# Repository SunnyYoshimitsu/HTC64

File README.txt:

# Y!6502
Think Ben Eater's 6502 but modified....a modified BE6592...the Y!6502....

I modified this computer to have 2 VIA chips instead of just one since I think having more GPIO will allow it to be used as a more conventional microcontroller. Also I changed the memory layout and add a larger RAM. So the memory layout ended up being inverted to Ben's, 32k of RAM and 16k of ROM. There's an expansion slot in the middle designed to take a stock Ben Eater's GPU with its !DMA config or any other peripherals you want. The expansion slot is mapped to A000 - BFFF. 

Note there's a VGA output and associtated resistors, however there are no GPU to drive it. This is for the expansion slot. I am planning a "modified" BE6502 GPU that uses a dual port RAM so that the CPU can run at 100% capacity. Now this computer is basically everything that the BE6502 is except for the GPU but ofcourse you don't have to populate everything. 

I'm porting Wozmon to this modifed BE6502 since the UART is in a different place and it does support a keyboard. I will update this repo as soon as I'm done with it. 

If you have any question or ideas please don't hesitate to hit me up! I am an active user in the r/beneater subreddit. 
Profile: https://www.reddit.com/user/YoshimitsuSunny

Memory Layout: 
	Note: each section is 8k in size
0000 - 1FFF: RAM
2000 - 3FFF: RAM 
4000 - 5FFF: RAM 
6000 - 7FFF: RAM
8000 - 9FFF: DDRAM 
A000 - BFFF: Peripheral
A200 - UART
A400 - A40F: I/O Timer 1
  Reg A: GPIO
  Reg B: P/S 2
A800 - A80F: I/O Timer 2
  Reg A: GPIO
  Reg B: GPIO
C000 - DFFF: ROM (lower address) 
E000 - FFFF: ROM (higher address)

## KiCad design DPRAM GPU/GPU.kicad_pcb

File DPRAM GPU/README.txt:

The PCB version is incomplete!!!!!! Don't use it. I'll fix it at a later date. However, the schematic should be correct. Have fun!

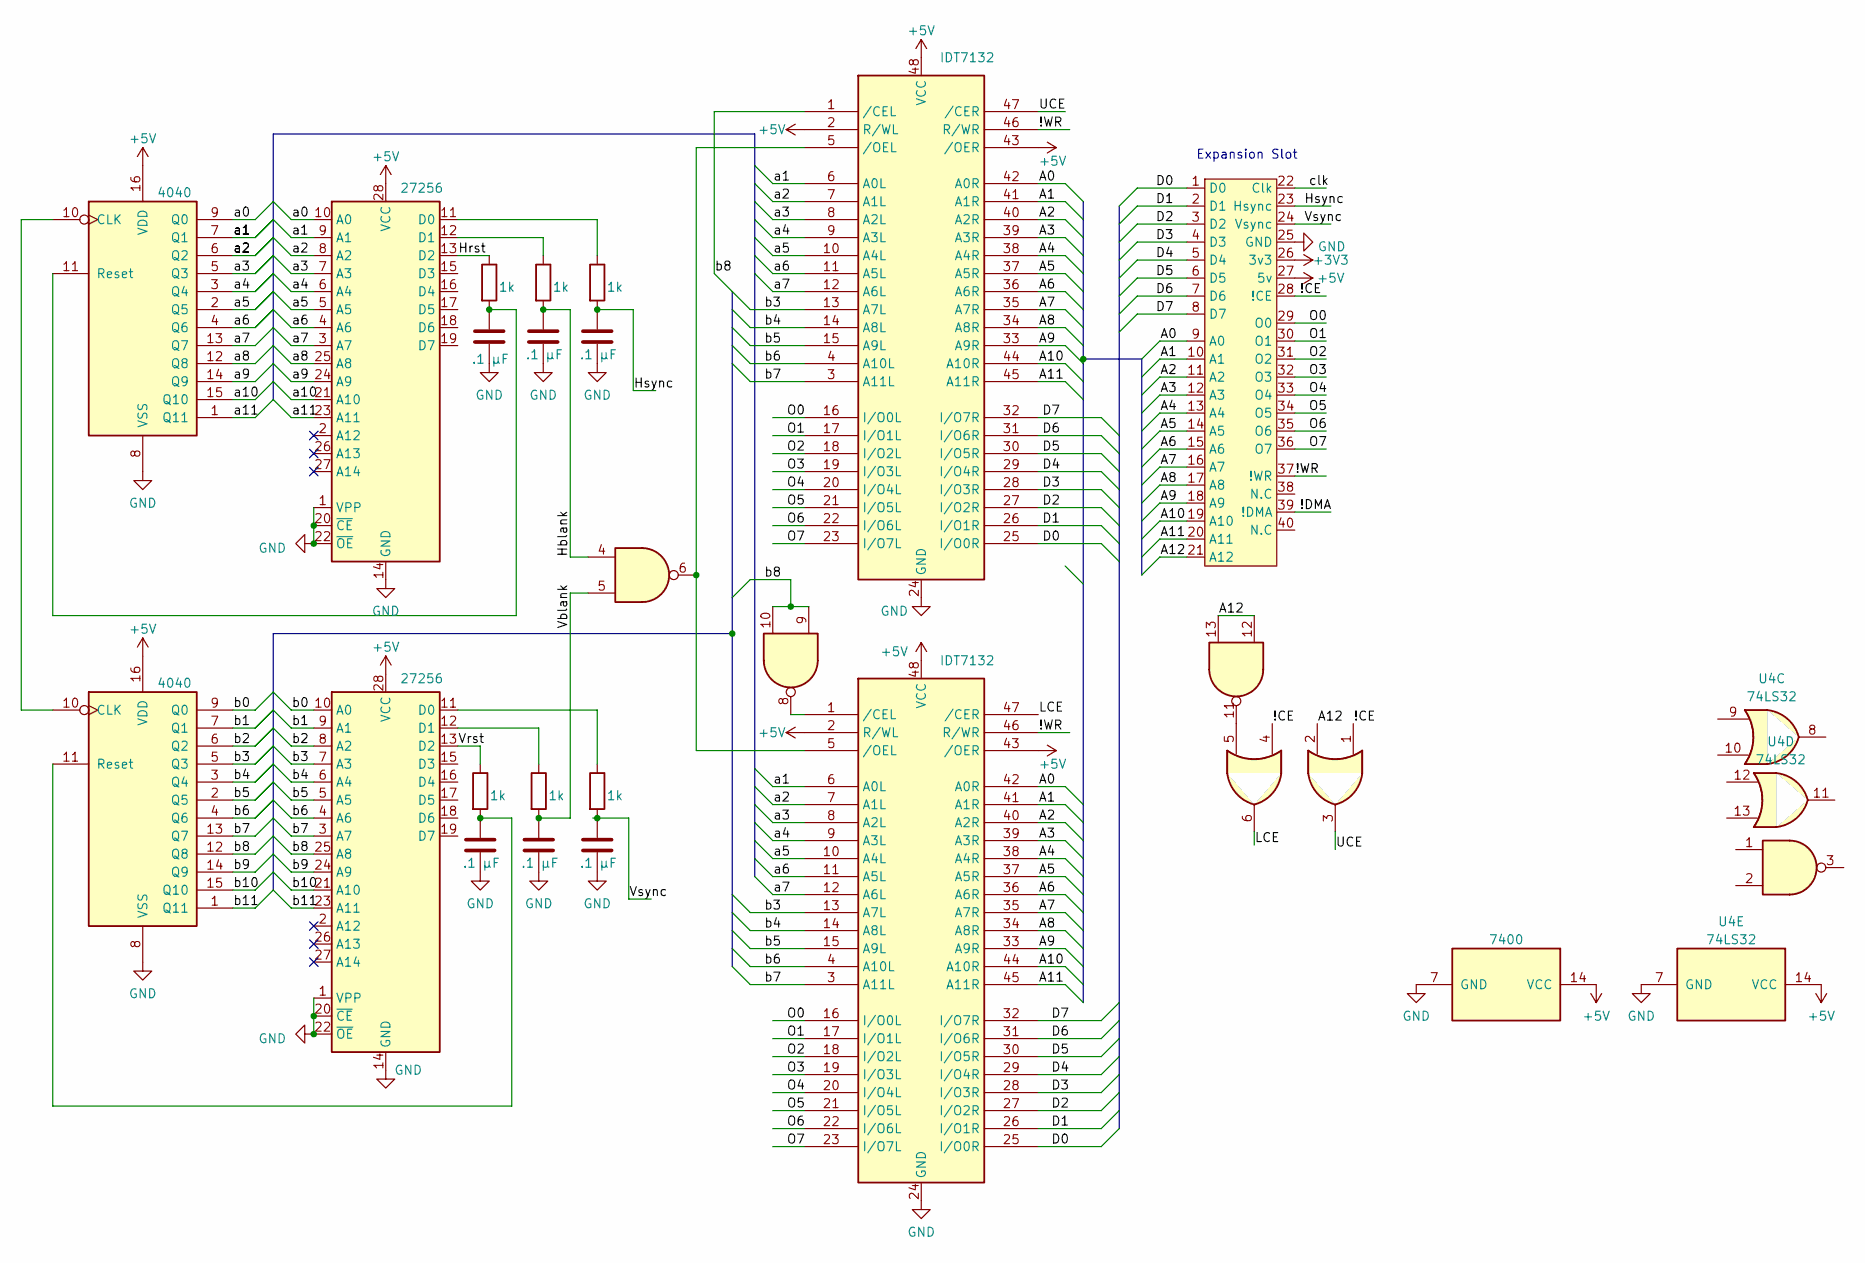
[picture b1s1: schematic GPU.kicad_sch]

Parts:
C1, C2, C3, C4, C5, C6: .1 μF; C_Disc_D3.4mm_W2.1mm_P2.50mm
R1, R2, R3, R4, R5, R6: 1k; R_Axial_DIN0207_L6.3mm_D2.5mm_P7.62mm_Horizontal
U1, U3: 4040; DIP-16_W7.62mm_Socket
U2, U8: 27256; DIP-28_W15.24mm_Socket
U4: 74LS32; DIP-14_W7.62mm
U5, U6: IDT7132; DIP-48_W15.24mm_Socket
U7: 7400; DIP-14_W7.62mm_Socket
~1: Y!6502 exp

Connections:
+5V: U1.16 (VDD), U2.28 (VCC), U3.16 (VDD), U4.14 (VCC), U5.2 (R/WL), U5.43 (/OER), U5.48 (VCC), U6.2 (R/WL), U6.43 (/OER), U6.48 (VCC), U7.14 (VCC), U8.28 (VCC), ~1.27 (5v)
/!CE: U4.1, U4.4, ~1.28 (!CE)
/!WR: U5.46 (R/WR), U6.46 (R/WR), ~1.37 (!WR)
/A0: U5.42 (A0R), U6.42 (A0R), ~1.9 (A0)
/A1: U5.41 (A1R), U6.41 (A1R), ~1.10 (A1)
/A2: U5.40 (A2R), U6.40 (A2R), ~1.11 (A2)
/A3: U5.39 (A3R), U6.39 (A3R), ~1.12 (A3)
/A4: U5.38 (A4R), U6.38 (A4R), ~1.13 (A4)
/A5: U5.37 (A5R), U6.37 (A5R), ~1.14 (A5)
/A6: U5.36 (A6R), U6.36 (A6R), ~1.15 (A6)
/A7: U5.35 (A7R), U6.35 (A7R), ~1.16 (A7)
/A8: U5.34 (A8R), U6.34 (A8R), ~1.17 (A8)
/A9: U5.33 (A9R), U6.33 (A9R), ~1.18 (A9)
/A10: U5.44 (A10R), U6.44 (A10R), ~1.19 (A10)
/A11: U5.45 (A11R), U6.45 (A11R), ~1.20 (A11)
/A12: U4.2, U7.12, U7.13, ~1.21 (A12)
/D0: U5.25 (I/O0R), U6.25 (I/O0R), ~1.1 (D0)
/D1: U5.26 (I/O1R), U6.26 (I/O1R), ~1.2 (D1)
/D2: U5.27 (I/O2R), U6.27 (I/O2R), ~1.3 (D2)
/D3: U5.28 (I/O3R), U6.28 (I/O3R), ~1.4 (D3)
/D4: U5.29 (I/O4R), U6.29 (I/O4R), ~1.5 (D4)
/D5: U5.30 (I/O5R), U6.30 (I/O5R), ~1.6 (D5)
/D6: U5.31 (I/O6R), U6.31 (I/O6R), ~1.7 (D6)
/D7: U5.32 (I/O7R), U6.32 (I/O7R), ~1.8 (D7)
/Hblank: C2.1, R2.2, U7.4
/Hrst: R1.1, U8.13 (D2)
/Hsync: C3.1, R3.2, ~1.23 (Hsync)
/LCE: U4.6, U6.47 (/CER)
/O0: U5.16 (I/O0L), U6.16 (I/O0L), ~1.29 (O0)
/O1: U5.17 (I/O1L), U6.17 (I/O1L), ~1.30 (O1)
/O2: U5.18 (I/O2L), U6.18 (I/O2L), ~1.31 (O2)
/O3: U5.19 (I/O3L), U6.19 (I/O3L), ~1.32 (O3)
/O4: U5.20 (I/O4L), U6.20 (I/O4L), ~1.33 (O4)
/O5: U5.21 (I/O5L), U6.21 (I/O5L), ~1.34 (O5)
/O6: U5.22 (I/O6L), U6.22 (I/O6L), ~1.35 (O6)
/O7: U5.23 (I/O7L), U6.23 (I/O7L), ~1.36 (O7)
/UCE: U4.3, U5.47 (/CER)
/Vblank: C5.1, R5.2, U7.5
/Vrst: R4.1, U2.13 (D2)
/Vsync: C6.1, R6.2, ~1.24 (Vsync)
/a0: U1.9 (Q0), U8.10 (A0)
/a1: U1.7 (Q1), U5.6 (A0L), U6.6 (A0L), U8.9 (A1)
/a2: U1.6 (Q2), U5.7 (A1L), U6.7 (A1L), U8.8 (A2)
/a3: U1.5 (Q3), U5.8 (A2L), U6.8 (A2L), U8.7 (A3)
/a4: U1.3 (Q4), U5.9 (A3L), U6.9 (A3L), U8.6 (A4)
/a5: U1.2 (Q5), U5.10 (A4L), U6.10 (A4L), U8.5 (A5)
/a6: U1.4 (Q6), U5.11 (A5L), U6.11 (A5L), U8.4 (A6)
/a7: U1.13 (Q7), U5.12 (A6L), U6.12 (A6L), U8.3 (A7)
/a8: U1.12 (Q8), U8.25 (A8)
/a9: U1.14 (Q9), U8.24 (A9)
/a10: U1.15 (Q10), U8.21 (A10)
/a11: U1.1 (Q11), U8.23 (A11)
/b0: U2.10 (A0), U3.9 (Q0)
/b1: U2.9 (A1), U3.7 (Q1)
/b2: U2.8 (A2), U3.6 (Q2)
/b3: U2.7 (A3), U3.5 (Q3), U5.13 (A7L), U6.13 (A7L)
/b4: U2.6 (A4), U3.3 (Q4), U5.14 (A8L), U6.14 (A8L)
/b5: U2.5 (A5), U3.2 (Q5), U5.15 (A9L), U6.15 (A9L)
/b6: U2.4 (A6), U3.4 (Q6), U5.4 (A10L), U6.4 (A10L)
/b7: U2.3 (A7), U3.13 (Q7), U5.3 (A11L), U6.3 (A11L)
/b8: U2.25 (A8), U3.12 (Q8), U5.1 (/CEL), U7.9, U7.10
/b9: U2.24 (A9), U3.14 (Q9)
/b10: U2.21 (A10), U3.15 (Q10)
/b11: U2.23 (A11), U3.1 (Q11)
GND: C1.2, C2.2, C3.2, C4.2, C5.2, C6.2, U1.8 (VSS), U2.1 (VPP), U2.14 (GND), U2.20 (~CE), U2.22 (~OE), U3.8 (VSS), U4.7 (GND), U5.24 (GND), U6.24 (GND), U7.7 (GND), U8.1 (VPP), U8.14 (GND), U8.20 (~CE), U8.22 (~OE), ~1.25 (GND)
unnamed: U1.10 (CLK), U3.10 (CLK)
unnamed: C1.1, R1.2, U1.11 (Reset)
unnamed: R6.1, U2.11 (D0)
unnamed: R5.1, U2.12 (D1)
unnamed: C4.1, R4.2, U3.11 (Reset)
unnamed: U4.5, U7.11
unnamed: U5.5 (/OEL), U6.5 (/OEL), U7.6
unnamed: U6.1 (/CEL), U7.8
unnamed: R3.1, U8.11 (D0)
unnamed: R2.1, U8.12 (D1)

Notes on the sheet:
Expansion Slot

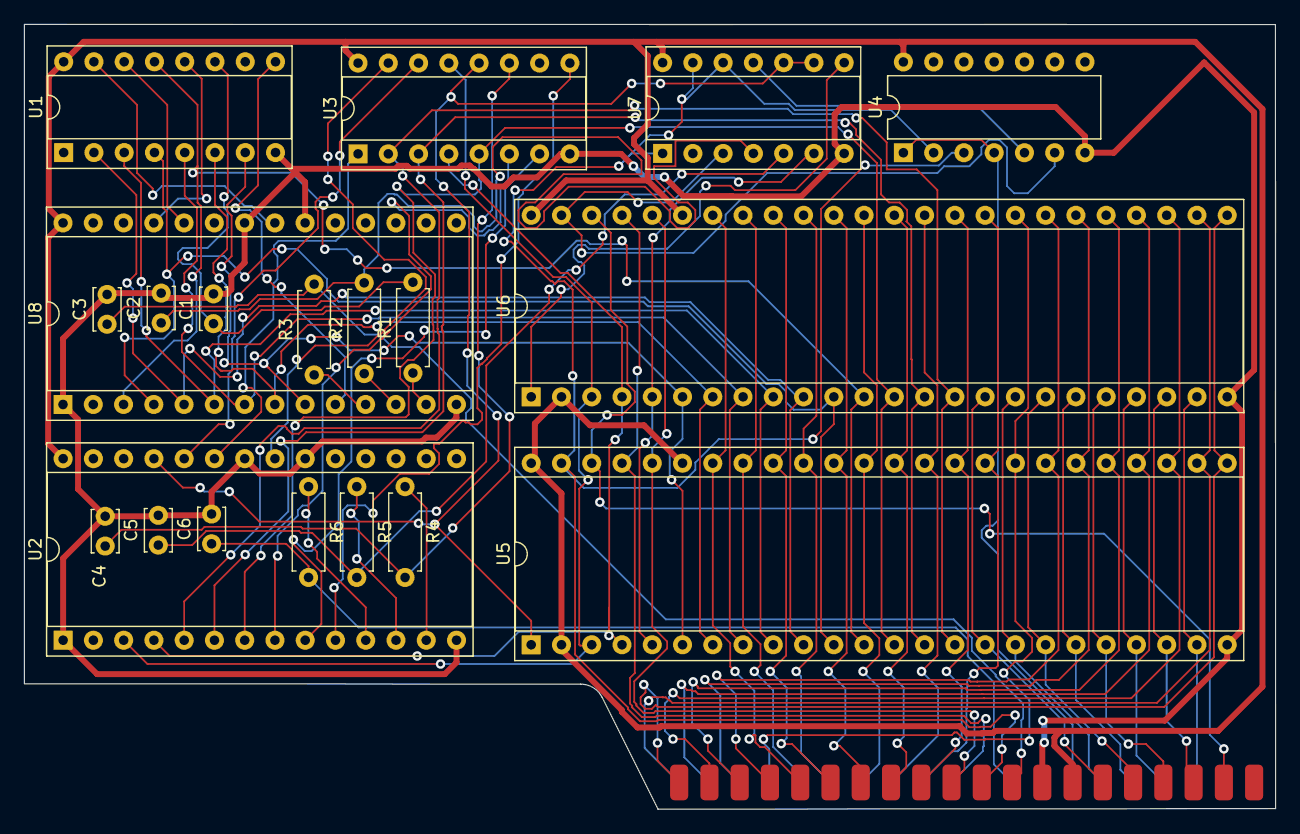
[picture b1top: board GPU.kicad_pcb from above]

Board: 2 copper layers, 105.0 x 65.9 mm, 20 parts (0 on the bottom side), 75 nets.

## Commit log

2023-07-05 second commit
2023-07-07 third commit
2023-07-07 fourth commit
2023-07-10 fifth commit
